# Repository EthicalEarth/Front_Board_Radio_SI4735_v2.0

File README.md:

# Front_Board_Radio_SI4735_v2.0
The front connection board for radio v2.0.

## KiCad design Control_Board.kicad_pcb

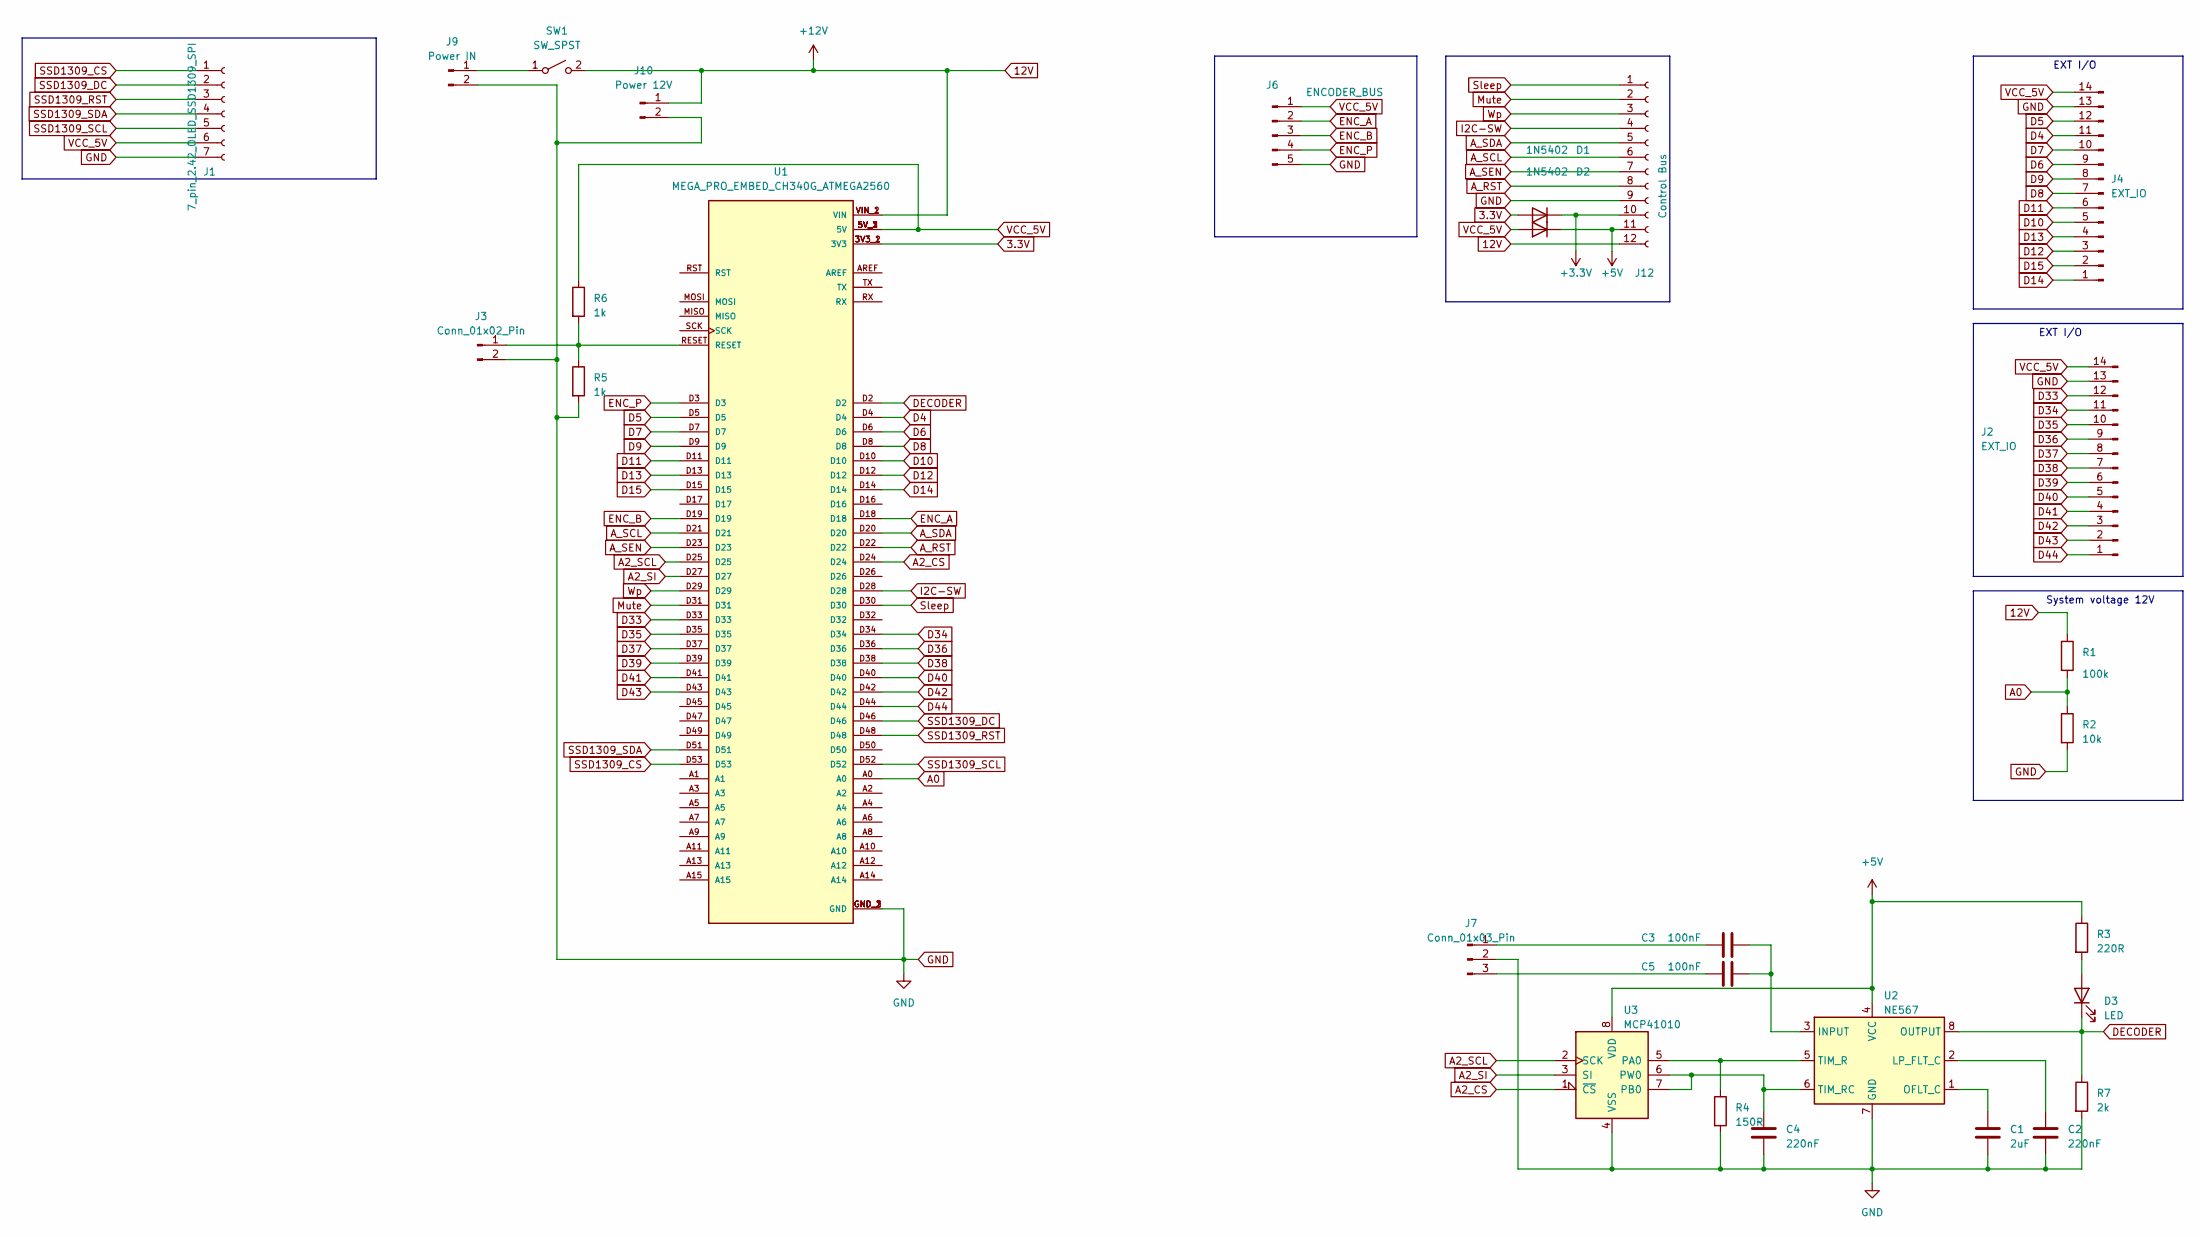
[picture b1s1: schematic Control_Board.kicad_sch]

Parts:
C1: 2uF; C_1206_3216Metric
C2, C4: 220nF; C_1206_3216Metric
C3, C5: 100nF; C_1206_3216Metric
D1, D2: 1N5402; D_1206_3216Metric
D3: LED; LED_D3.0mm_Clear
J1: 7_pin_2.42_OLED_SSD1309_SPI; PinSocket_1x07_P2.54mm_Vertical
J2, J4: EXT_IO; PinHeader_1x14_P2.54mm_Vertical
J3: Conn_01x02_Pin; PinHeader_1x02_P1.27mm_Vertical
J6: ENCODER_BUS; PinHeader_1x05_P2.54mm_Vertical
J7: Conn_01x03_Pin; PinHeader_1x03_P2.54mm_Vertical
J9: Power IN; PinSocket_1x02_P2.54mm_Vertical
J10: Power 12V; PinSocket_1x02_P2.54mm_Vertical
J12: Control Bus; PinSocket_1x12_P2.54mm_Horizontal
R1: 100k; R_1206_3216Metric
R2: 10k; R_1206_3216Metric
R3: 220R; R_1206_3216Metric
R4: 150R; R_1206_3216Metric
R5, R6: 1k; R_1206_3216Metric
R7: 2k; R_1206_3216Metric
SW1: SW_SPST; PinSocket_1x02_P2.54mm_Vertical
U1: MEGA_PRO_EMBED_CH340G_ATMEGA2560; MODULE_MEGA_PRO_EMBED_CH340G_ATMEGA2560; PARTREV 12/May/2017
U2: NE567; DIP-8_W7.62mm
U3: MCP41010; DIP-8_W7.62mm

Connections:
3.3V: D1.2 (A), U1.3V3_1 (3V3), U1.3V3_2 (3V3)
12V: J10.1, J12.12, R1.1, SW1.2 (B), U1.VIN_1 (VIN), U1.VIN_2 (VIN)
+3V3: D1.1 (K), J12.10
+5V: D2.1 (K), J12.11, R3.1, U2.4 (VCC), U3.8 (VDD)
A0: R1.2, R2.1, U1.A0
A2_CS: U1.D24, U3.1 (~CS)
A2_SCL: U1.D25, U3.2 (SCK)
A2_SI: U1.D27, U3.3 (SI)
A_RST: J12.8, U1.D22
A_SCL: J12.6, U1.D21
A_SDA: J12.5, U1.D20
A_SEN: J12.7, U1.D23
D4: J4.11, U1.D4
D5: J4.12, U1.D5
D6: J4.9, U1.D6
D7: J4.10, U1.D7
D8: J4.7, U1.D8
D9: J4.8, U1.D9
D10: J4.5, U1.D10
D11: J4.6, U1.D11
D12: J4.3, U1.D12
D13: J4.4, U1.D13
D14: J4.1, U1.D14
D15: J4.2, U1.D15
D33: J2.12, U1.D33
D34: J2.11, U1.D34
D35: J2.10, U1.D35
D36: J2.9, U1.D36
D37: J2.8, U1.D37
D38: J2.7, U1.D38
D39: J2.6, U1.D39
D40: J2.5, U1.D40
D41: J2.4, U1.D41
D42: J2.3, U1.D42
D43: J2.2, U1.D43
D44: J2.1, U1.D44
DECODER: D3.1 (K), R7.1, U1.D2, U2.8 (OUTPUT)
ENC_A: J6.2, U1.D18
ENC_B: J6.3, U1.D19
ENC_P: J6.4, U1.D3
GND: C1.2, C2.2, C4.2, J1.7, J2.13, J3.2, J4.13, J6.5, J7.2, J9.2, J10.2, J12.9, R2.2, R4.2, R5.2, R7.2, U1.GND_1 (GND), U1.GND_2 (GND), U1.GND_3 (GND), U2.7 (GND), U3.4 (VSS)
I2C-SW: J12.4, U1.D28
Mute: J12.2, U1.D31
unnamed: D3.2 (A), R3.2
unnamed: J3.1, R5.1, R6.2, U1.RESET
unnamed: C3.1, J7.1
unnamed: C5.1, J7.3
unnamed: J9.1, SW1.1 (A)
unnamed: C3.2, C5.2, U2.3 (INPUT)
unnamed: C2.1, U2.2 (LP_FLT_C)
unnamed: C1.1, U2.1 (OFLT_C)
unnamed: R4.1, U2.5 (TIM_R), U3.5 (PA0)
unnamed: C4.1, U2.6 (TIM_RC), U3.6 (PW0), U3.7 (PB0)
SSD1309_CS: J1.1, U1.D53
SSD1309_DC: J1.2, U1.D46
SSD1309_RST: J1.3, U1.D48
SSD1309_SCL: J1.5, U1.D52
SSD1309_SDA: J1.4, U1.D51
Sleep: J12.1, U1.D30
VCC_5V: D2.2 (A), J1.6, J2.14, J4.14, J6.1, R6.1, U1.5V_1 (5V), U1.5V_2 (5V), U1.5V_3 (5V)
Wp: J12.3, U1.D29

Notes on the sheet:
System voltage 12V
EXT I/O

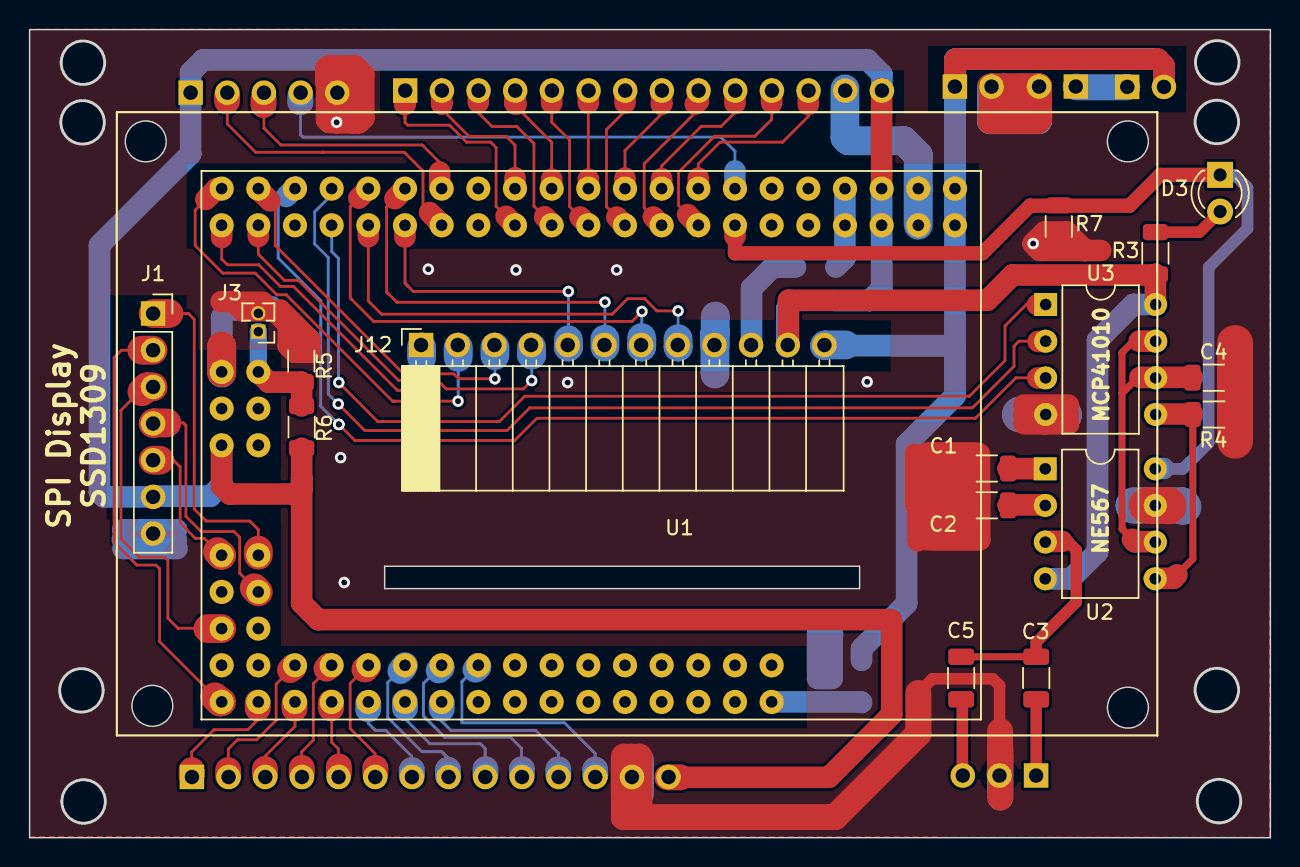
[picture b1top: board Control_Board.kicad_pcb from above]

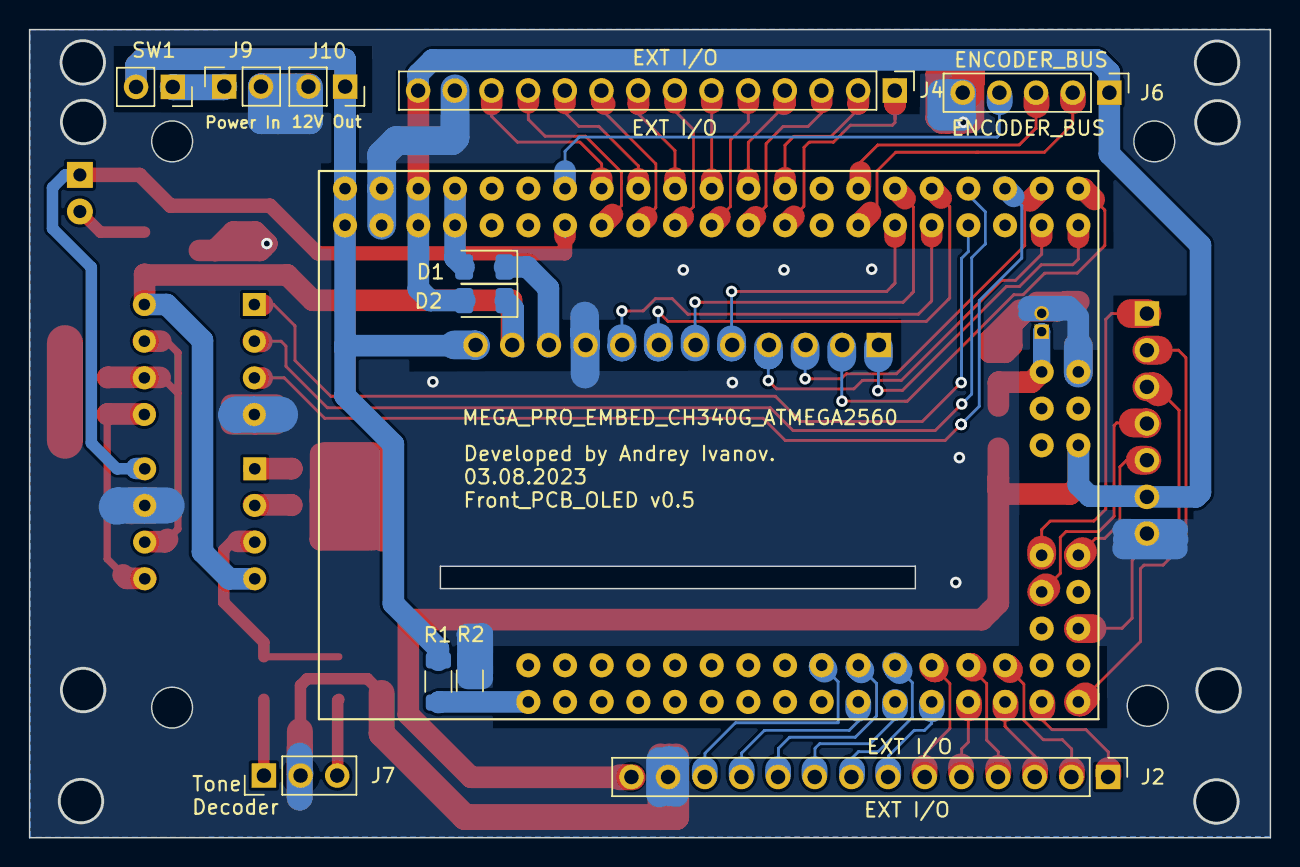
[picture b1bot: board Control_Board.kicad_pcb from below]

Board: 2 copper layers, 86.0 x 56.0 mm, 28 parts (11 on the bottom side), 61 nets.

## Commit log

2023-11-05 Init
